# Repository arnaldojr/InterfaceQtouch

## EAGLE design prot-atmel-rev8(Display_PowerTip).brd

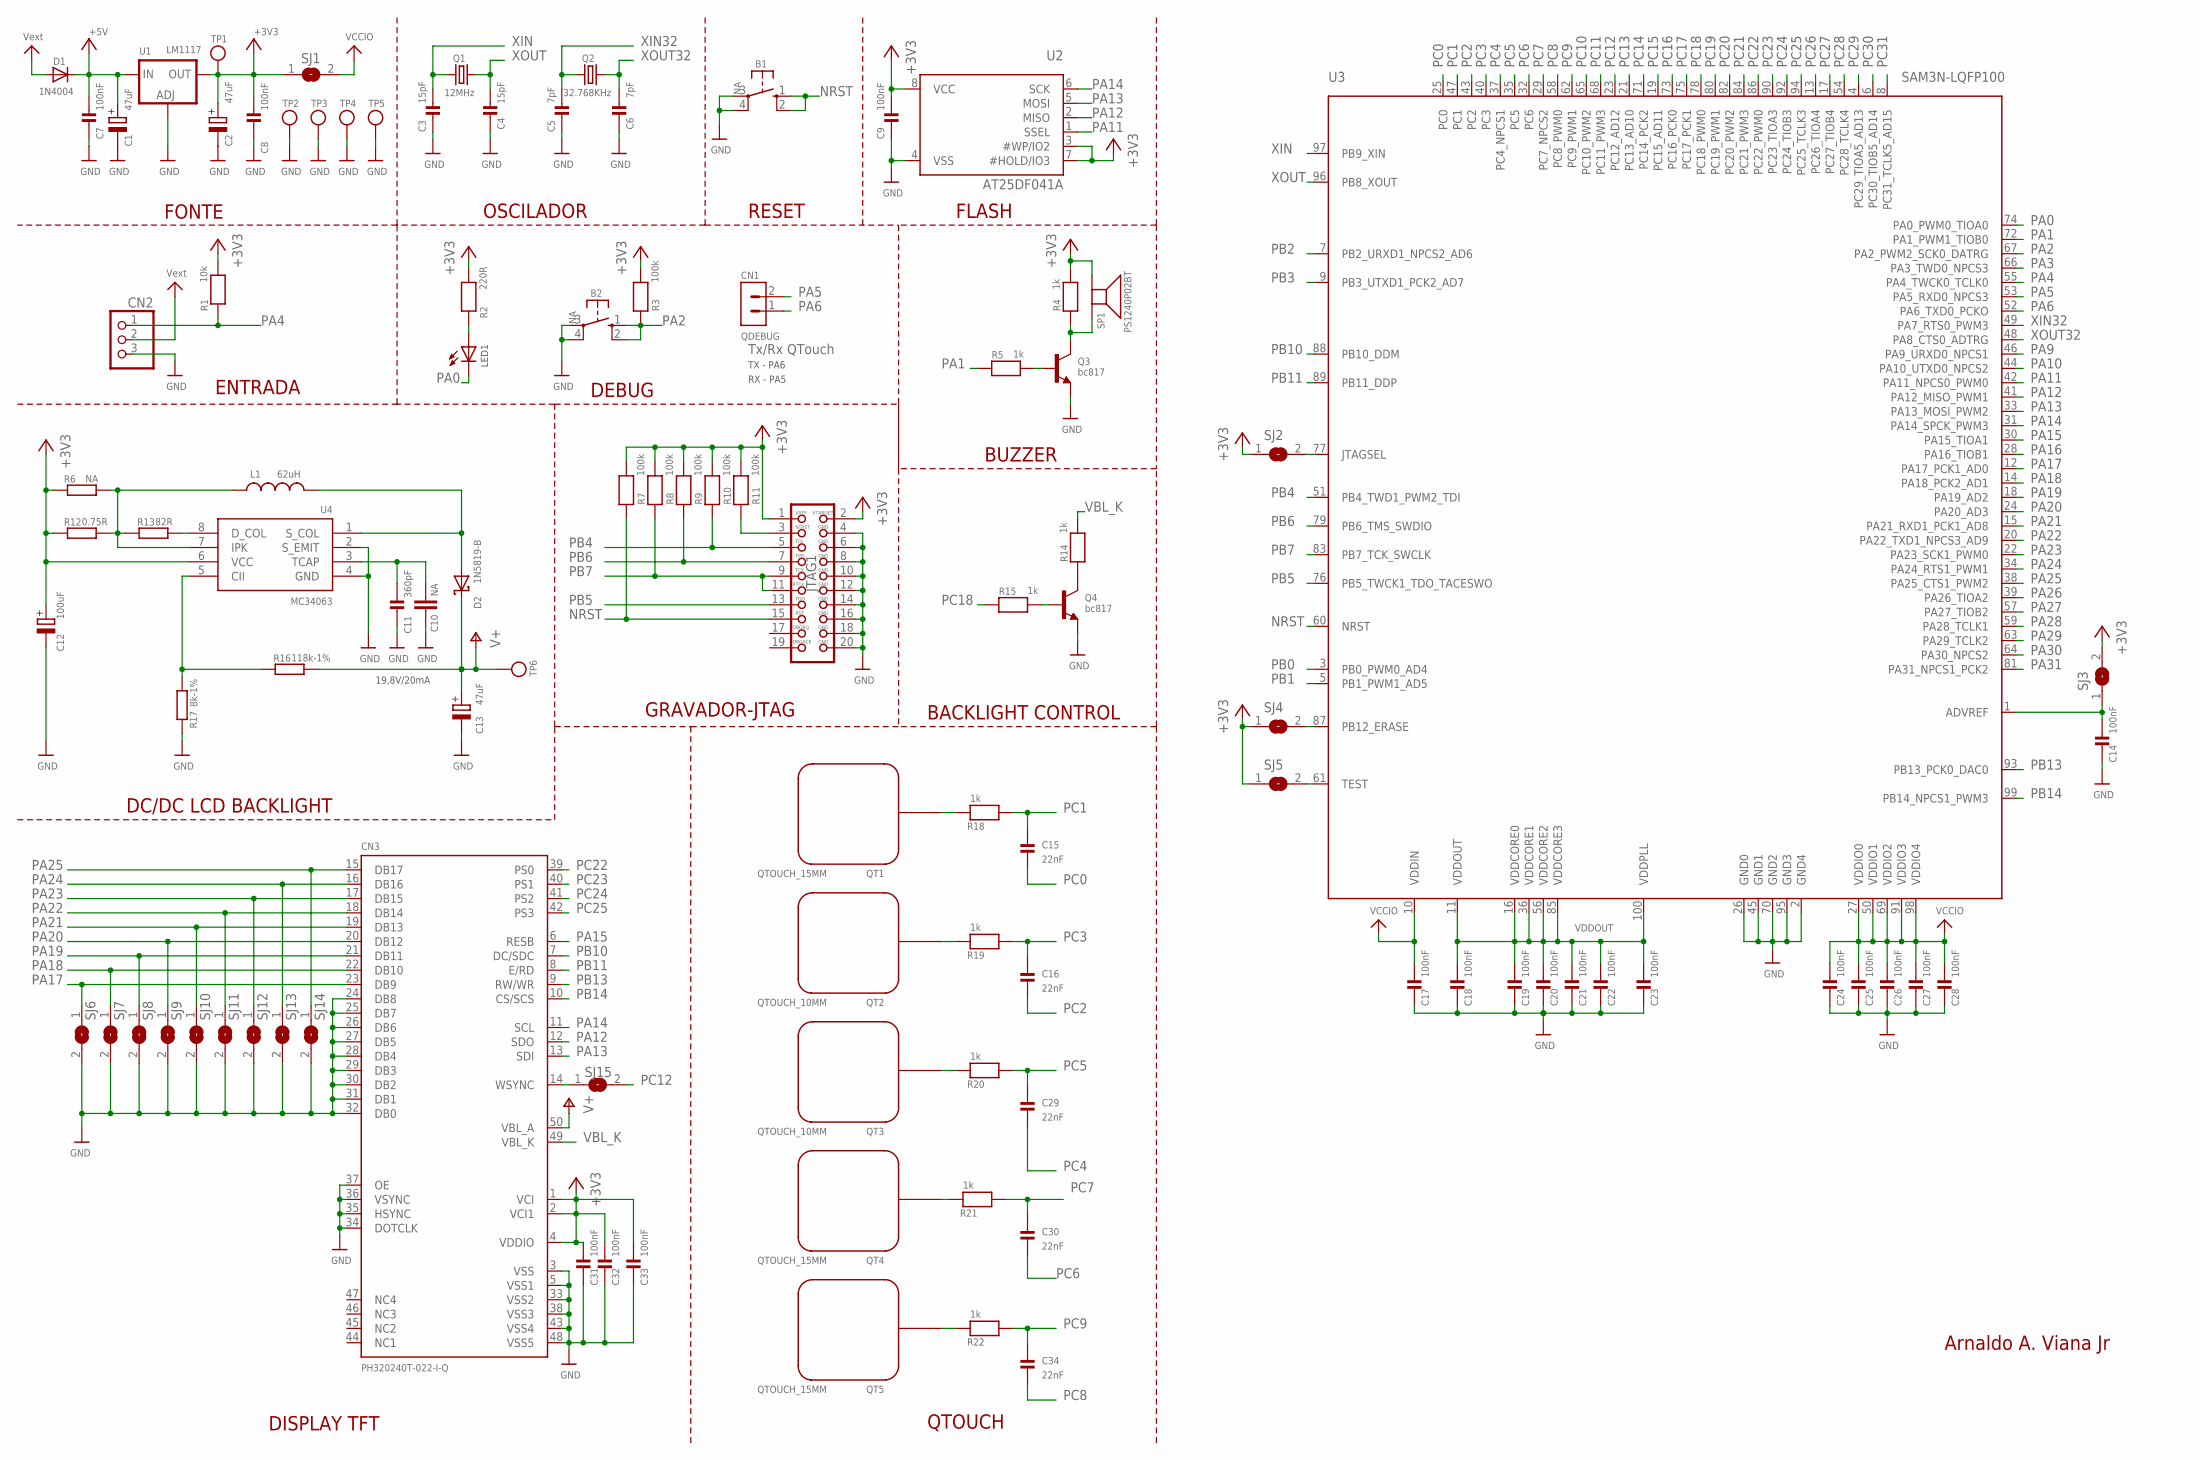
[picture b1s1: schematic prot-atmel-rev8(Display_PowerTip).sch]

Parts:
B1, B2: NA; B3F-10XX
C1, C2, C13: 47uF; E2,5-6
C3, C4: 15pF; 0805
C5, C6: 7pF; 0805
C7, C8, C9, C14, C17, C18, C19, C20, C21, C22, C23, C24, C25, C26, C27, C28, C31, C32, C33: 100nF; 0805
C10: NA; C025-025X050
C11: 360pF; 0805
C12: 100uF; E2,5-6
C15, C16, C29, C30, C34: 22nF; 0805
CN1: QDEBUG; HEADER_1X02
CN2: HEADER-1X3; 1X03_OVAL
CN3: PH320240T-022-I-Q; FPC50PIN_TFT-PH320240T
D1: 1N4004; D-5
D2: 1N5819-B; DO41-7.6
JTAG1: JTAG-ARM
L1: 62uH; 0204/5
LED1: LEDSML0805; SML0805
Q1: 12MHz; HC49/S
Q2: 32.768KHz; TC26V
Q3, Q4: bc817; SOT23-W
QT1, QT4, QT5: QTOUCH_15MM; BUTTON_15MM
QT2, QT3: QTOUCH_10MM; BUTTON_10MM
R1: 10k; _0805
R2: 220R; _0805
R3, R7, R8, R9, R10, R11: 100k; _0805
R4, R5, R14, R15, R18, R19, R20, R21, R22: 1k; _0805
R6: NA; 0204/5
R12: 0.75R; R1218
R13: 82R; M0805
R16: 118k-1%; M0805
R17: 8k-1%; M0805
SJ1, SJ2, SJ3, SJ4, SJ5, SJ6, SJ7, SJ8, SJ9, SJ10, SJ11, SJ12, SJ13, SJ14, SJ15: SOLDERJUMPER; SOLDERJUMPER_ARROW_NOPASTE
SP1: PS1240P02BT
TP1: +3V3; 1X01_ROUND
TP2, TP3, TP4, TP5: GND; 1X01_ROUND
TP6: +V; 1X01_ROUND
U1: LM1117; TO252
U2: AT25DF041A; SOIC8_208MIL
U3: SAM3N-LQFP100; LQFP100
U4: MC34063; SOIC8_150MIL

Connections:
12V: CN2.2, D1.A
+3V3: C2.+, C8.1, C9.1, C12.+, C31.1, C32.1, C33.1, CN3.1 (VCI), CN3.2 (VCI1), CN3.4 (VDDIO), JTAG1.1, JTAG1.2, R1.2, R2.2, R3.2, R4.2, R6.1, R7.2, R8.2, R9.2, R10.2, R11.2, R12.1, SJ1.1, SJ2.1, SJ3.2, SJ4.1, SJ5.1, SP1.P$2, TP1.1, U1.3 (OUT), U2.3 (#WP/IO2), U2.7 (#HOLD/IO3), U2.8 (VCC), U4.6 (VCC)
+5V: C1.+, C7.1, D1.C, U1.2 (IN)
ADVREF: C14.1, SJ3.1, U3.1 (ADVREF)
GND: B1.3, B1.4 (P1), B2.3, B2.4 (P1), C1.-, C2.-, C3.2, C4.2, C5.2, C6.2, C7.2, C8.2, C9.2, C10.2, C11.2, C12.-, C13.-, C14.2, C17.2, C18.2, C19.2, C20.2, C21.2, C22.2, C23.2, C24.2, C25.2, C26.2, C27.2, C28.2, C31.2, C32.2, C33.2, CN2.3, CN3.3 (VSS), CN3.5 (VSS1), CN3.24 (DB8), CN3.25 (DB7), CN3.26 (DB6), CN3.27 (DB5), CN3.28 (DB4), CN3.29 (DB3), CN3.30 (DB2), CN3.31 (DB1), CN3.32 (DB0), CN3.33 (VSS2), CN3.34 (DOTCLK), CN3.35 (HSYNC), CN3.36 (VSYNC), CN3.37 (OE), CN3.38 (VSS3), CN3.43 (VSS4), CN3.48 (VSS5), JTAG1.4, JTAG1.6, JTAG1.8, JTAG1.10, JTAG1.12, JTAG1.14, JTAG1.16, JTAG1.18, JTAG1.20, Q3.2 (E), Q4.2 (E), R17.1, SJ6.2, SJ7.2, SJ8.2, SJ9.2, SJ10.2, SJ11.2, SJ12.2, SJ13.2, SJ14.2, TP2.1, TP3.1, TP4.1, TP5.1, U1.1 (ADJ), U2.4 (VSS), U3.2 (GND4), U3.26 (GND0), U3.45 (GND1), U3.70 (GND2), U3.95 (GND3), U4.2 (S_EMIT), U4.4 (GND)
unnamed: Q4.1 (B), R15.2
unnamed: Q4.3 (C), R14.1
unnamed: SJ2.2, U3.77 (JTAGSEL)
unnamed: CN3.14 (WSYNC), SJ15.1
unnamed: JTAG1.3, R11.1
unnamed: QT2.P$1, R19.2
unnamed: QT3.P$1, R20.2
unnamed: QT4.P$1, R21.2
unnamed: LED1.A, R2.1
unnamed: QT5.P$1, R22.2
unnamed: SJ4.2, U3.87 (PB12_ERASE)
unnamed: Q3.1 (B), R5.1
unnamed: Q3.3 (C), R4.1, SP1.P$1
unnamed: SJ5.2, U3.61 (TEST)
unnamed: R13.2, U4.8 (D_COL)
unnamed: L1.1, R6.2, R12.2, R13.1, U4.7 (IPK)
unnamed: R16.1, R17.2, U4.5 (CII)
unnamed: D2.A, L1.2, U4.1 (S_COL)
unnamed: C10.1, C11.1, U4.3 (TCAP)
unnamed: QT1.P$1, R18.2
NRST: B1.1 (S), B1.2 (S1), JTAG1.15, R7.1, U3.60 (NRST)
PA0: LED1.C, U3.74 (PA0_PWM0_TIOA0)
PA1: R5.2, U3.72 (PA1_PWM1_TIOB0)
PA2: B2.1 (S), B2.2 (S1), R3.1, U3.67 (PA2_PWM2_SCK0_DATRG)
PA3: U3.66 (PA3_TWD0_NPCS3)
PA4: CN2.1, R1.1, U3.55 (PA4_TWCK0_TCLK0)
PA5: CN1.2, U3.53 (PA5_RXD0_NPCS3)
PA6: CN1.1, U3.52 (PA6_TXD0_PCKO)
PA9: U3.46 (PA9_URXD0_NPCS1)
PA10: U3.44 (PA10_UTXD0_NPCS2)
PA11: U2.1 (SSEL), U3.42 (PA11_NPCS0_PWM0)
PA12: CN3.12 (SDO), U2.2 (MISO), U3.41 (PA12_MISO_PWM1)
PA13: CN3.13 (SDI), U2.5 (MOSI), U3.33 (PA13_MOSI_PWM2)
PA14: CN3.11 (SCL), U2.6 (SCK), U3.31 (PA14_SPCK_PWM3)
PA15: CN3.6 (RESB), U3.30 (PA15_TIOA1)
PA16: U3.28 (PA16_TIOB1)
PA17: CN3.23 (DB9), SJ6.1, U3.12 (PA17_PCK1_AD0)
PA18: CN3.22 (DB10), SJ7.1, U3.14 (PA18_PCK2_AD1)
PA19: CN3.21 (DB11), SJ8.1, U3.18 (PA19_AD2)
PA20: CN3.20 (DB12), SJ9.1, U3.24 (PA20_AD3)
PA21: CN3.19 (DB13), SJ10.1, U3.15 (PA21_RXD1_PCK1_AD8)
PA22: CN3.18 (DB14), SJ11.1, U3.20 (PA22_TXD1_NPCS3_AD9)
PA23: CN3.17 (DB15), SJ12.1, U3.22 (PA23_SCK1_PWM0)
PA24: CN3.16 (DB16), SJ13.1, U3.34 (PA24_RTS1_PWM1)
PA25: CN3.15 (DB17), SJ14.1, U3.38 (PA25_CTS1_PWM2)
PA26: U3.39 (PA26_TIOA2)
PA27: U3.57 (PA27_TIOB2)
PA28: U3.59 (PA28_TCLK1)
PA29: U3.63 (PA29_TCLK2)
PA30: U3.64 (PA30_NPCS2)
PA31: U3.81 (PA31_NPCS1_PCK2)
PB0: U3.3 (PB0_PWM0_AD4)
PB1: U3.5 (PB1_PWM1_AD5)
PB2: U3.7 (PB2_URXD1_NPCS2_AD6)
PB3: U3.9 (PB3_UTXD1_PCK2_AD7)
PB4: JTAG1.5, R10.1, U3.51 (PB4_TWD1_PWM2_TDI)
PB5: JTAG1.13, U3.76 (PB5_TWCK1_TDO_TACESWO)
PB6: JTAG1.7, R9.1, U3.79 (PB6_TMS_SWDIO)
PB7: JTAG1.9, JTAG1.11, R8.1, U3.83 (PB7_TCK_SWCLK)
PB10: CN3.7 (DC/SDC), U3.88 (PB10_DDM)
PB11: CN3.8 (E/RD), U3.89 (PB11_DDP)
PB13: CN3.9 (RW/WR), U3.93 (PB13_PCK0_DAC0)
PB14: CN3.10 (CS/SCS), U3.99 (PB14_NPCS1_PWM3)
PC0: C15.2, U3.25 (PC0)
PC1: C15.1, R18.1, U3.47 (PC1)
PC2: C16.2, U3.43 (PC2)
PC3: C16.1, R19.1, U3.40 (PC3)
PC4: C29.2, U3.37 (PC4_NPCS1)
PC5: C29.1, R20.1, U3.35 (PC5)
PC6: C30.2, U3.32 (PC6)
PC7: C30.1, R21.1, U3.29 (PC7_NPCS2)
PC8: C34.2, U3.58 (PC8_PWM0)
PC9: C34.1, R22.1, U3.62 (PC9_PWM1)
PC10: U3.65 (PC10_PWM2)
PC11: U3.68 (PC11_PWM3)
PC12: SJ15.2, U3.23 (PC12_AD12)
PC13: U3.21 (PC13_AD10)
PC14: U3.71 (PC14_PCK2)
PC15: U3.19 (PC15_AD11)
PC16: U3.73 (PC16_PCK0)
PC17: U3.75 (PC17_PCK1)
PC18: R15.1, U3.78 (PC18_PWM0)
PC19: U3.80 (PC19_PWM1)
PC20: U3.82 (PC20_PWM2)
PC21: U3.84 (PC21_PWM3)
PC22: CN3.39 (PS0), U3.86 (PC22_PWM0)
PC23: CN3.40 (PS1), U3.90 (PC23_TIOA3)
PC24: CN3.41 (PS2), U3.92 (PC24_TIOB3)
PC25: CN3.42 (PS3), U3.94 (PC25_TCLK3)
PC26: U3.13 (PC26_TIOA4)
PC27: U3.17 (PC27_TIOB4)
PC28: U3.54 (PC28_TCLK4)
PC29: U3.4 (PC29_TIOA5_AD13)
PC30: U3.6 (PC30_TIOB5_AD14)
PC31: U3.8 (PC31_TCLK5_AD15)
V+: C13.+, CN3.50 (VBL_A), D2.C, R16.2, TP6.1
VBL_K: CN3.49 (VBL_K), R14.2
VCCIO: C17.1, C24.1, C25.1, C26.1, C27.1, C28.1, SJ1.2, U3.10 (VDDIN), U3.27 (VDDIO0), U3.50 (VDDIO1), U3.69 (VDDIO2), U3.91 (VDDIO3), U3.98 (VDDIO4)
VDDOUT: C18.1, C19.1, C20.1, C21.1, C22.1, C23.1, U3.11 (VDDOUT), U3.16 (VDDCORE0), U3.36 (VDDCORE1), U3.56 (VDDCORE2), U3.85 (VDDCORE3), U3.100 (VDDPLL)
XIN: C3.1, Q1.1, U3.97 (PB9_XIN)
XIN32: C5.1, Q2.1, U3.49 (PA7_RTS0_PWM3)
XOUT: C4.1, Q1.2, U3.96 (PB8_XOUT)
XOUT32: C6.1, Q2.2, U3.48 (PA8_CTS0_ADTRG)

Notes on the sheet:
DISPLAY TFT
FONTE
GRAVADOR-JTAG
RESET
QTOUCH
OSCILADOR
DEBUG
DC/DC LCD BACKLIGHT
Arnaldo A. Viana Jr
BUZZER
FLASH
ENTRADA
Tx/Rx QTouch
BACKLIGHT CONTROL
19,8V/20mA
RX - PA5
TX - PA6

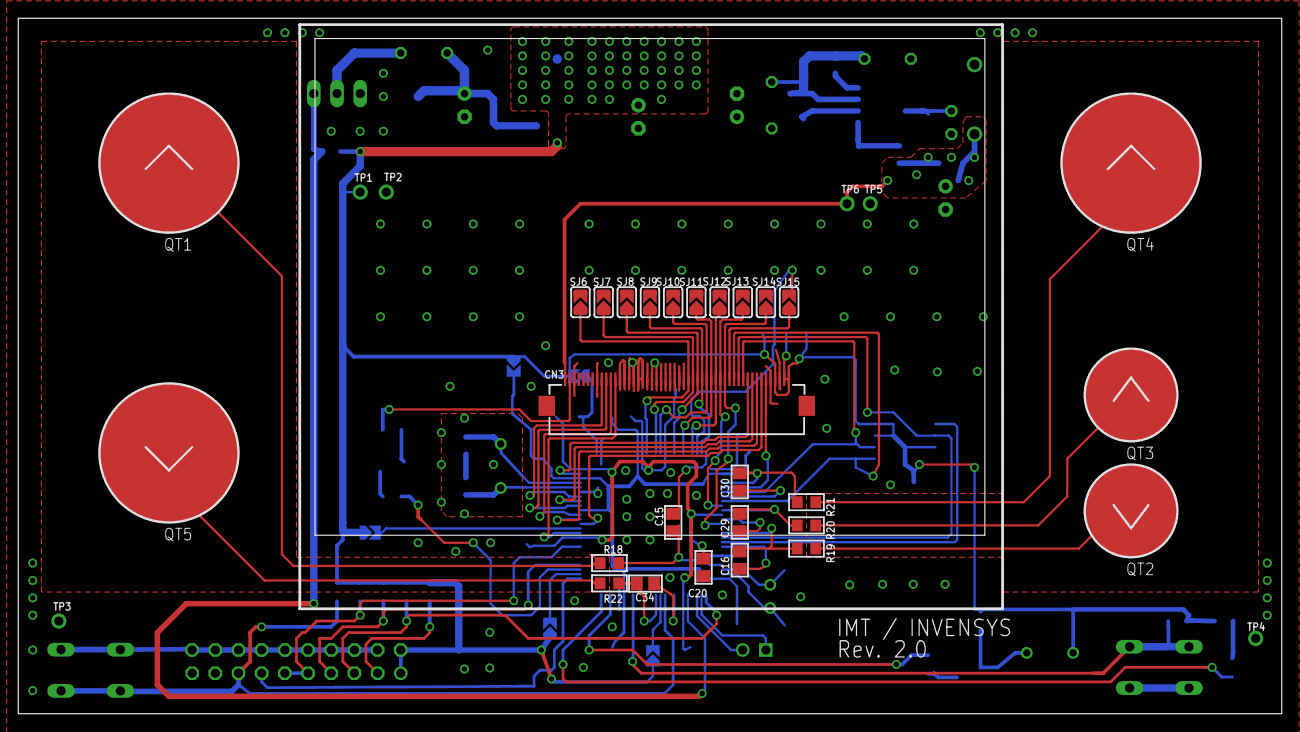
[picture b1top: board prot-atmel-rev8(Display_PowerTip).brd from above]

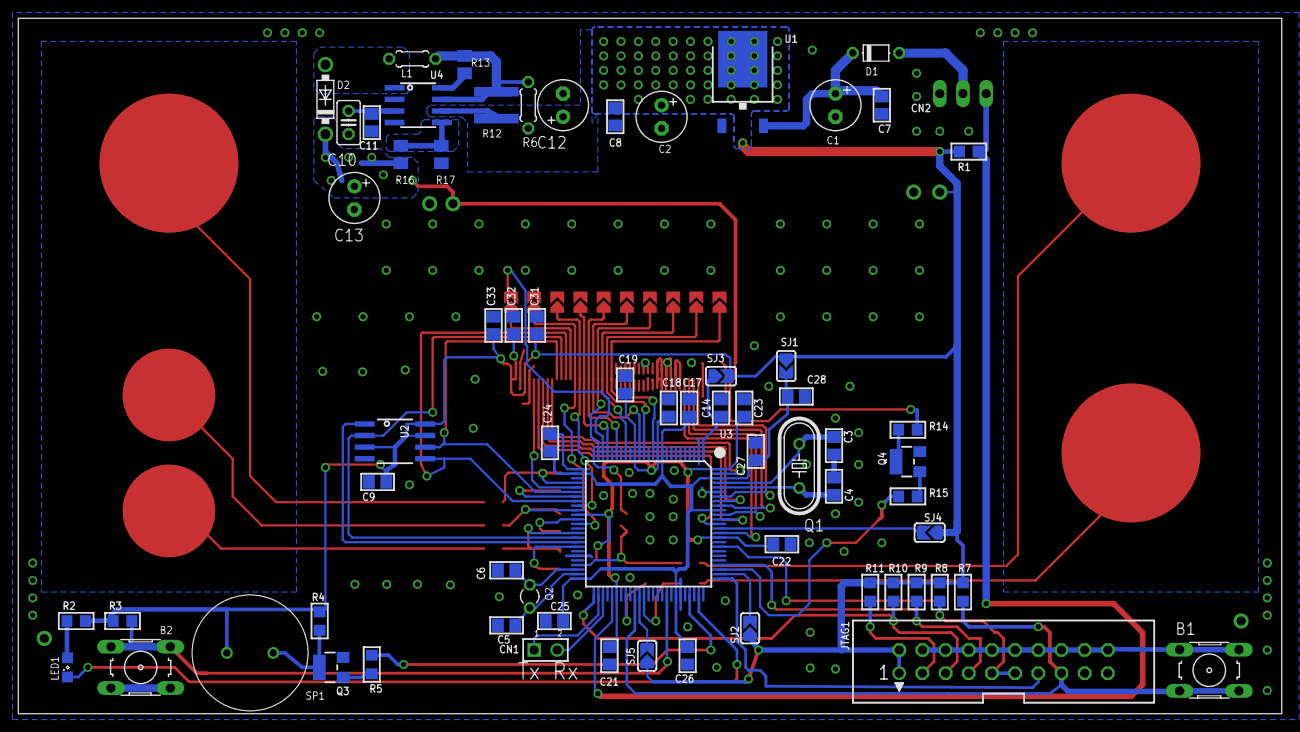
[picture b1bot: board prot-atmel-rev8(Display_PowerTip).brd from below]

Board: 2 copper layers, 138.4 x 76.2 mm, 103 parts (69 on the bottom side), 78 nets.

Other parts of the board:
U$9, U$13: LOGO_MAUA

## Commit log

2018-11-02 init commit

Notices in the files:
parts and their libraries:
junior: This work is placed in the public domain, and may be freely used for commercial and non-commercial work with the following conditions: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
